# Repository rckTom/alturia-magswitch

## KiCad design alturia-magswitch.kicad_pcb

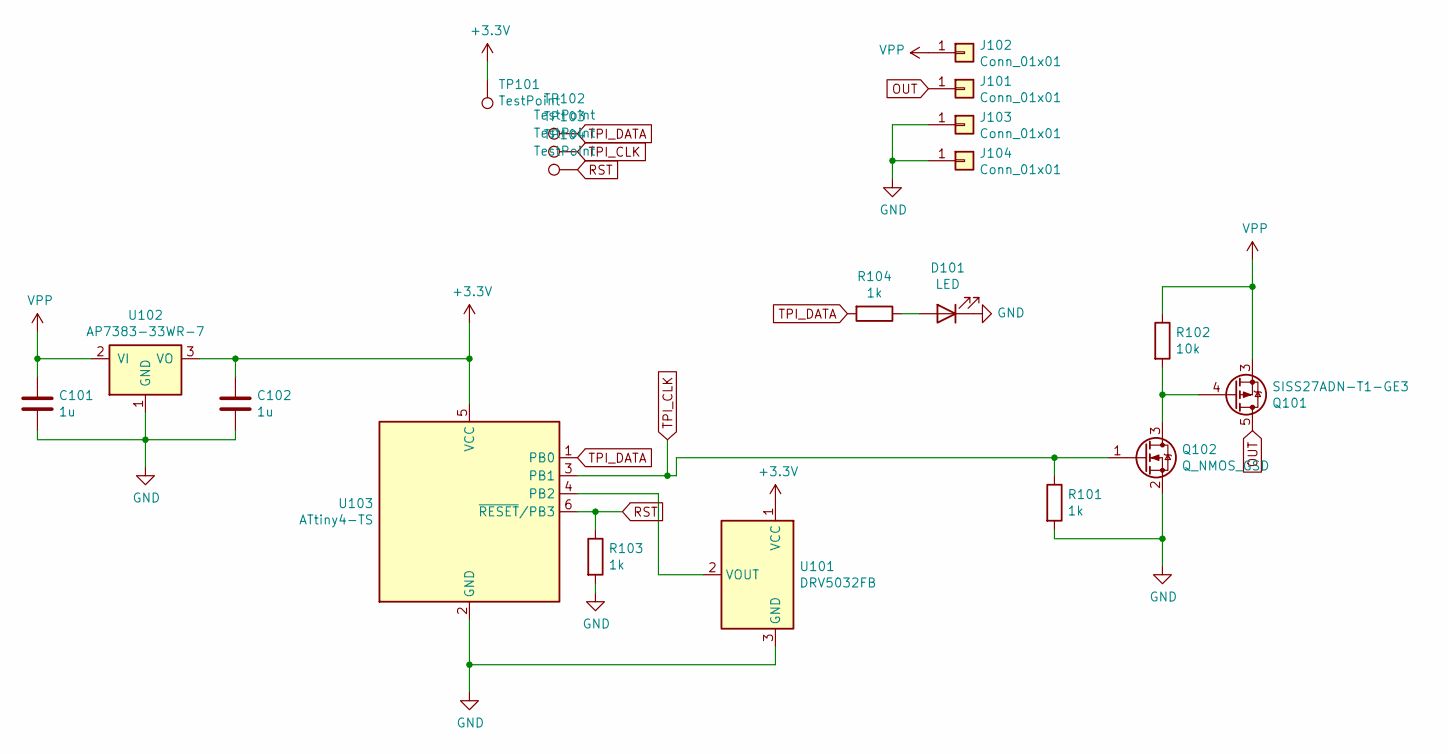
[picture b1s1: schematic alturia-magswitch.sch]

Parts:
C101, C102: 1u; C_0603_1608Metric
D101: LED; LED_0603_1608Metric
J101, J102, J103, J104: Conn_01x01; SolderWire-1.5sqmm_1x01_D1.7mm_OD3.9mm
Q101: SISS27ADN-T1-GE3; Vishay_PowerPAK_1212-8_Single; Partnumber SI7149ADP
Q102: Q_NMOS_GSD; SOT-323_SC-70; Partnumber NX7002AKW
R101, R103, R104: 1k; R_0402_1005Metric
R102: 10k; R_0402_1005Metric
TP101, TP102, TP103, TP104: TestPoint; TestPoint_Pad_D1.0mm
U101: DRV5032FB; SOT-23; Partnumber DRV5032FB
U102: AP7383-33WR-7; SOIC-6; Partnumber AP7383-33WR-7
U103: ATtiny4-TS; SOT-23-6; Partnumber ATTINY4-TS8R

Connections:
+3V3: C102.1, TP101.1, U101.1 (VCC), U102.3 (VO), U103.5 (VCC)
GND: C101.2, C102.2, D101.1 (K), J103.1, J104.1, Q102.2 (S), R101.2, R103.2, U101.3 (GND), U102.1 (GND), U103.2 (GND)
unnamed: D101.2 (A), R104.1
unnamed: Q101.4 (G), Q102.3 (D), R102.2
unnamed: U101.2 (VOUT), U103.4 (PB2)
OUT: J101.1, Q101.5 (D)
RST: R103.1, TP104.1, U103.6 (~RESET~/PB3)
TPI_CLK: Q102.1 (G), R101.1, TP103.1, U103.3 (PB1)
TPI_DATA: R104.2, TP102.1, U103.1 (PB0)
VPP: C101.1, J102.1, Q101.1 (S), Q101.2 (S), Q101.3 (S), R102.1, U102.2 (VI)

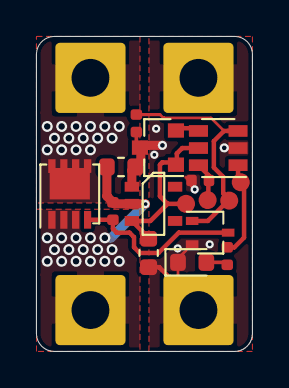
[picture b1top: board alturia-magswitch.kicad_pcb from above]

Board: 2 copper layers, 12.0 x 17.5 mm, 20 parts (0 on the bottom side), 10 nets.

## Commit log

2020-06-11 add a panel
2020-07-04 fix wrongly connected power mosfet
2020-07-04 add a programming jig
2020-07-04 add firmware

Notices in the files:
alturia-magswitch.kicad_pcb:
CC BY-SA 4.0
